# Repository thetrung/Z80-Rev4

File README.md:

# Z80 Homebrew with PIC18/F4520 
Rev4 of Z80 + PIC18/F4520 setup.

### Note
I have never had a real working Z80 before so this board is designed to test that if I can get one.

### 3D Preview 

### Placement (SilkScreen)

### Schematic

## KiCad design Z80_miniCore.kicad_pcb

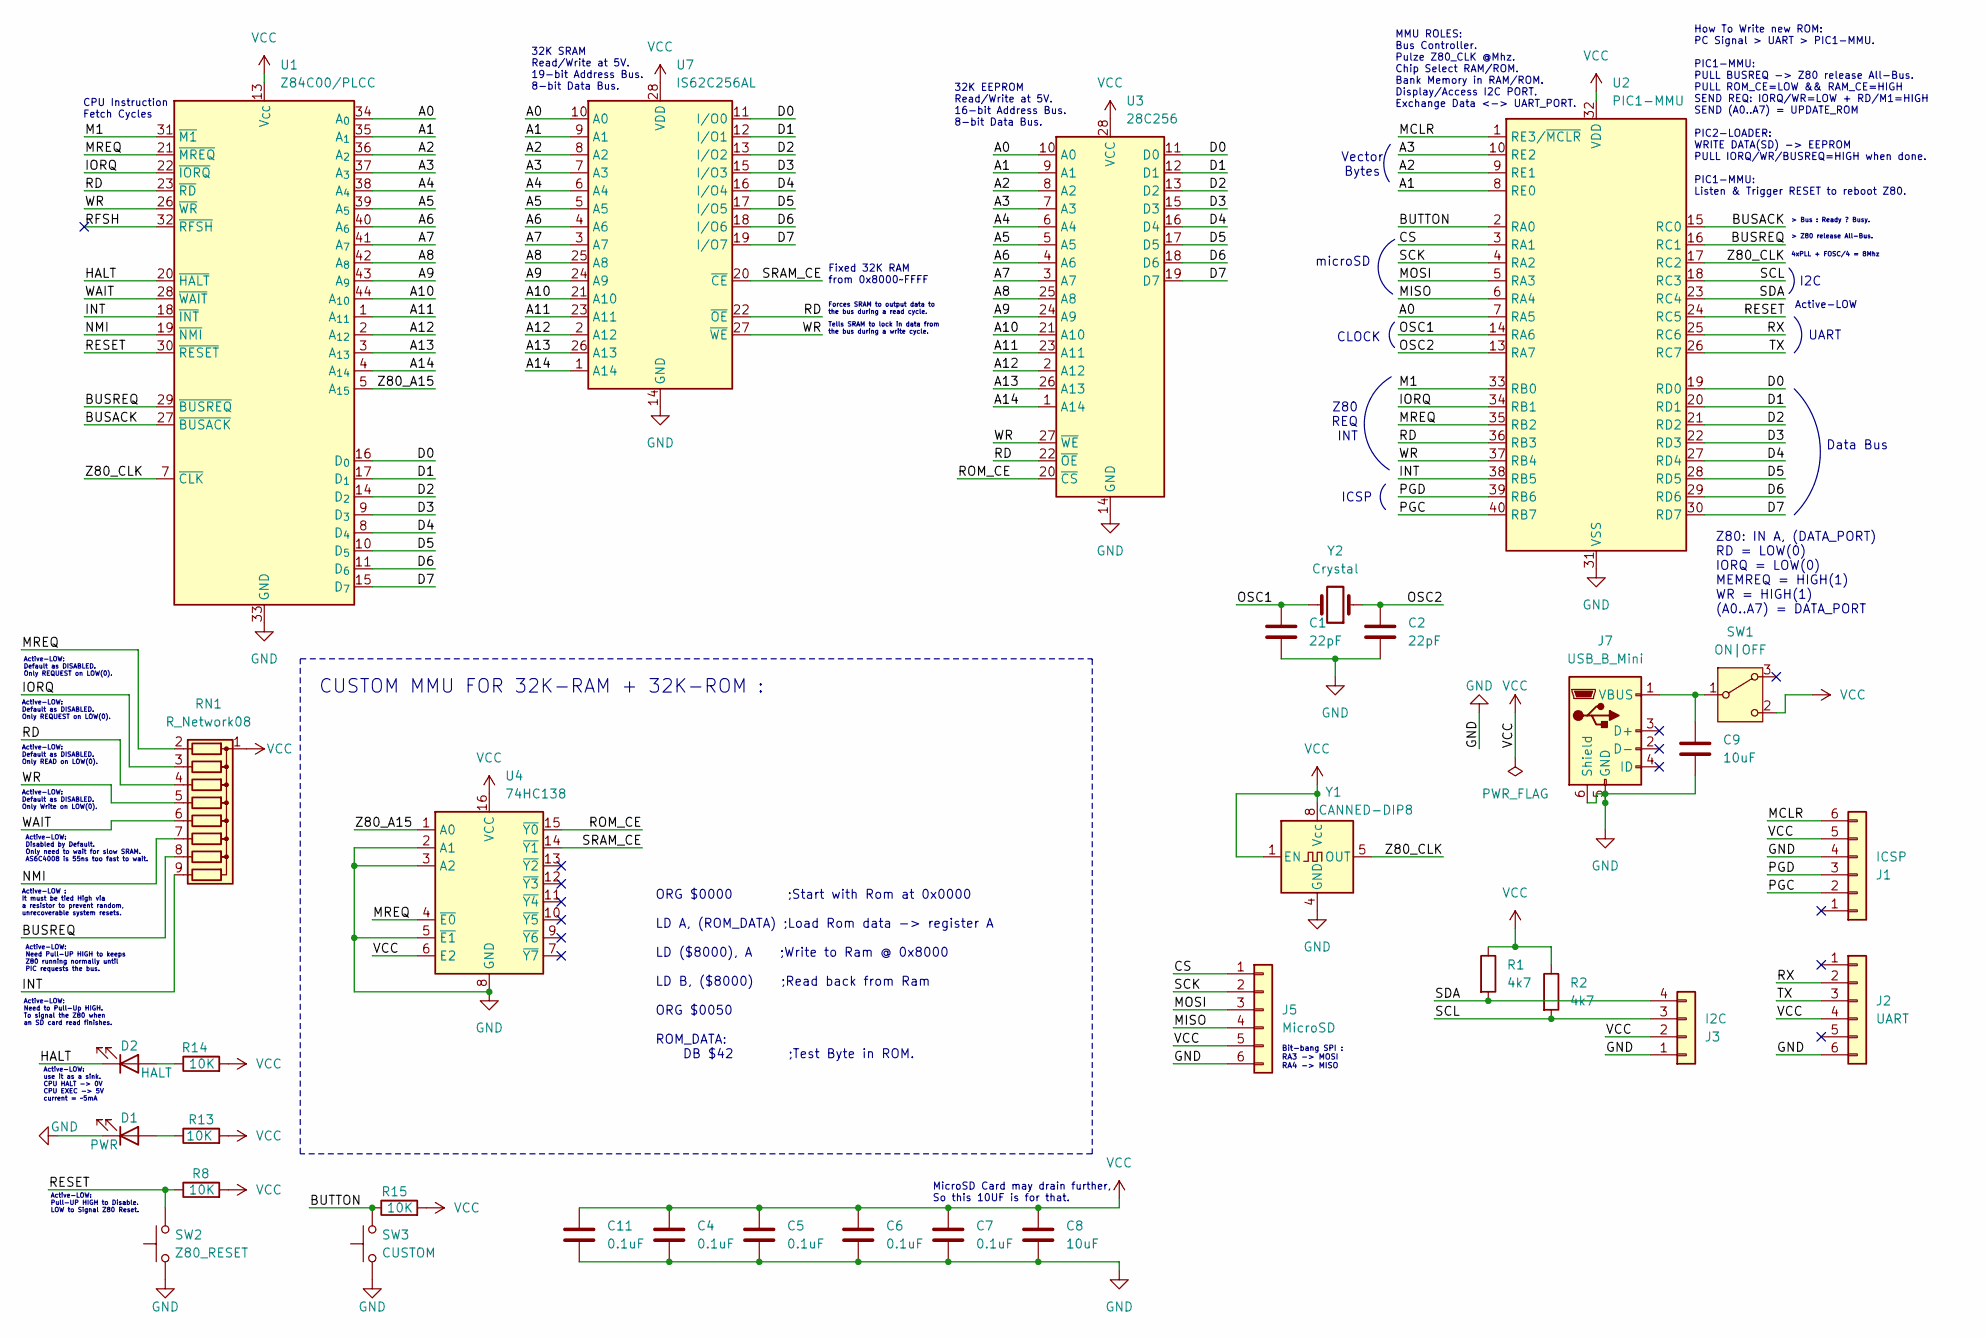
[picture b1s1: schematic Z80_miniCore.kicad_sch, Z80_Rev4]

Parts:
C1, C2: 22pF; C_Disc_D3.4mm_W2.1mm_P2.50mm
C4, C5, C6, C7, C11: 0.1uF; C_Disc_D3.4mm_W2.1mm_P2.50mm
C8, C9: 10uF; C_Radial_D4.0mm_H5.0mm_P1.50mm
D1: PWR; LED_D3.0mm
D2: HALT; LED_D3.0mm
J1: ICSP; PinHeader_1x06_P2.54mm_Horizontal
J2: UART; PinHeader_1x06_P2.54mm_Vertical
J3: I2C; PinHeader_1x04_P2.54mm_Vertical
J5: MicroSD; PinHeader_1x06_P2.54mm_Vertical
J7: USB_B_Mini; USB_MINI_B_90_Angled
R1, R2: 4k7; R_Axial_DIN0207_L6.3mm_D2.5mm_P10.16mm_Horizontal
R8, R13, R14, R15: 10K; R_Axial_DIN0207_L6.3mm_D2.5mm_P10.16mm_Horizontal
RN1: R_Network08; R_Array_SIP9
SW1: ON|OFF; SW_Slide-03_Wuerth-WS-SLTV_10x2.5x6.4_P2.54mm
SW2: Z80_RESET; SW_PUSH_6mm
SW3: CUSTOM; SW_PUSH_6mm
U1: Z84C00/PLCC; PLCC-44_THT-Socket
U2: PIC1-MMU; DIP-40_W15.24mm
U3: 28C256; DIP-28_W15.24mm
U4: 74HC138; DIP-16_W7.62mm
U7: IS62C256AL; DIP-28_W15.24mm
Y1: CANNED-DIP8; Oscillator_DIP-8
Y2: Crystal; Crystal_HC49-4H_Vertical

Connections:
/A0: U1.34 (A_{0}), U2.7 (RA5), U3.10 (A0), U7.10 (A0)
/A1: U1.35 (A_{1}), U2.8 (RE0), U3.9 (A1), U7.9 (A1)
/A2: U1.36 (A_{2}), U2.9 (RE1), U3.8 (A2), U7.8 (A2)
/A3: U1.37 (A_{3}), U2.10 (RE2), U3.7 (A3), U7.7 (A3)
/A4: U1.38 (A_{4}), U3.6 (A4), U7.6 (A4)
/A5: U1.39 (A_{5}), U3.5 (A5), U7.5 (A5)
/A6: U1.40 (A_{6}), U3.4 (A6), U7.4 (A6)
/A7: U1.41 (A_{7}), U3.3 (A7), U7.3 (A7)
/A8: U1.42 (A_{8}), U3.25 (A8), U7.25 (A8)
/A9: U1.43 (A_{9}), U3.24 (A9), U7.24 (A9)
/A10: U1.44 (A_{10}), U3.21 (A10), U7.21 (A10)
/A11: U1.1 (A_{11}), U3.23 (A11), U7.23 (A11)
/A12: U1.2 (A_{12}), U3.2 (A12), U7.2 (A12)
/A13: U1.3 (A_{13}), U3.26 (A13), U7.26 (A13)
/A14: U1.4 (A_{14}), U3.1 (A14), U7.1 (A14)
/BUSACK: U1.27 (~BUSACK), U2.15 (RC0)
/BUSREQ: RN1.8 (R7), U1.29 (~BUSREQ), U2.16 (RC1)
/BUTTON: R15.1, SW3.2, U2.2 (RA0)
/CS: J5.1, U2.3 (RA1)
/D0: U1.16 (D_{0}), U2.19 (RD0), U3.11 (D0), U7.11 (I/O0)
/D1: U1.17 (D_{1}), U2.20 (RD1), U3.12 (D1), U7.12 (I/O1)
/D2: U1.14 (D_{2}), U2.21 (RD2), U3.13 (D2), U7.13 (I/O2)
/D3: U1.9 (D_{3}), U2.22 (RD3), U3.15 (D3), U7.15 (I/O3)
/D4: U1.8 (D_{4}), U2.27 (RD4), U3.16 (D4), U7.16 (I/O4)
/D5: U1.10 (D_{5}), U2.28 (RD5), U3.17 (D5), U7.17 (I/O5)
/D6: U1.11 (D_{6}), U2.29 (RD6), U3.18 (D6), U7.18 (I/O6)
/D7: U1.15 (D_{7}), U2.30 (RD7), U3.19 (D7), U7.19 (I/O7)
/HALT: D2.1 (K), U1.20 (~HALT)
/INT: RN1.9 (R8), U1.18 (~INT), U2.38 (RB5)
/IORQ: RN1.3 (R2), U1.22 (~IORQ), U2.34 (RB1)
/M1: U1.31 (~M1), U2.33 (RB0)
/MCLR: J1.6, U2.1 (RE3/~MCLR)
/MISO: J5.4, U2.6 (RA4)
/MOSI: J5.3, U2.5 (RA3)
/MREQ: RN1.2 (R1), U1.21 (~MREQ), U2.35 (RB2), U4.4 (~E0)
/NMI: RN1.7 (R6), U1.19 (~NMI)
/OSC1: C1.1, U2.14 (RA6), Y2.2
/OSC2: C2.1, U2.13 (RA7), Y2.1
/PGC: J1.2, U2.40 (RB7)
/PGD: J1.3, U2.39 (RB6)
/RD: RN1.4 (R3), U1.23 (~RD), U2.36 (RB3), U3.22 (~OE), U7.22 (~OE)
/RESET: R8.1, SW2.2, U1.30 (~RESET), U2.24 (RC5)
/RFSH: U1.32 (~RFSH)
/ROM_CE: U3.20 (~CS), U4.15 (~Y0)
/RX: J2.2, U2.25 (RC6)
/SCK: J5.2, U2.4 (RA2)
/SCL: J3.3, R2.2, U2.18 (RC3)
/SDA: J3.4, R1.2, U2.23 (RC4)
/SRAM_CE: U4.14 (~Y1), U7.20 (~CE)
/TX: J2.3, U2.26 (RC7)
/WAIT: RN1.6 (R5), U1.28 (~WAIT)
/WR: RN1.5 (R4), U1.26 (~WR), U2.37 (RB4), U3.27 (~WE), U7.27 (~WE)
/Z80_A15: U1.5 (A_{15}), U4.1 (A0)
/Z80_CLK: U1.7 (~CLK), U2.17 (RC2), Y1.5 (OUT)
GND: C1.2, C2.2, C4.1, C5.1, C6.1, C7.1, C8.1, C9.1, C11.1, D1.1 (K), J1.4, J2.6, J3.1, J5.6, J7.5 (GND), J7.6 (Shield), SW2.1, SW3.1, U1.33 (GND), U2.12 (VSS), U2.31 (VSS), U3.14 (GND), U4.2 (A1), U4.3 (A2), U4.5 (~E1), U4.8 (GND), U7.14 (GND), Y1.4 (GND)
unnamed: D1.2 (A), R13.1
unnamed: D2.2 (A), R14.1
unnamed: C9.2, J7.1 (VBUS), SW1.1 (B)
VCC: C4.2, C5.2, C6.2, C7.2, C8.2, C11.2, J1.5, J2.4, J3.2, J5.5, R1.1, R2.1, R8.2, R13.2, R14.2, R15.2, RN1.1 (common), SW1.2 (C), U1.13 (V_{CC}), U2.11 (VDD), U2.32 (VDD), U3.28 (VCC), U4.6 (E2), U4.16 (VCC), U7.28 (VDD), Y1.1 (EN), Y1.8 (Vcc)

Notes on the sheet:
microSD
Active-LOW: Default as DISABLED. Only REQUEST on LOW(0).
Active-LOW: Need to Pull-Up HIGH. To signal the Z80 when an SD card read finishes.
Tells SRAM to lock in data from the bus during a write cycle.
32K SRAM Read/Write at 5V. 19-bit Address Bus. 8-bit Data Bus.
Active-LOW: use it as a sink. CPU HALT -> 0V CPU EXEC -> 5V current = ~5mA
Active-LOW: Default as DISABLED. Only READ on LOW(0).
ICSP
CLOCK
> Bus : Ready ? Busy.
ORG $0000 ;Start with Rom at 0x0000 LD A, (ROM_DATA) ;Load Rom data -> register A LD ($8000), A ;Write to Ram @ 0x8000 LD B, ($8000) ;Read back from Ram ORG $0050 ROM_DATA: DB $42 ;Test Byte in ROM.
Data Bus
Z80 REQ INT
Forces SRAM to output data to the bus during a read cycle.
MMU ROLES: Bus Controller. Pulze Z80_CLK @Mhz. Chip Select RAM/ROM. Bank Memory in RAM/ROM. Display/Access I2C PORT. Exchange Data <-> UART_PORT.
32K EEPROM Read/Write at 5V. 16-bit Address Bus. 8-bit Data Bus.
Active-LOW: Disabled by Default. Only need to wait for slow SRAM. AS6C4008 is 55ns too fast to wait.
Active-LOW: Need Pull-UP HIGH to keeps Z80 running normally until PIC requests the bus.
I2C
MicroSD Card may drain further, So this 10UF is for that.
Active-LOW : It must be tied High via a resistor to prevent random, unrecoverable system resets.
Active-LOW: Pull-UP HIGH to Disable. LOW to Signal Z80 Reset.
4xPLL + FOSC/4 = 8Mhz
Active-LOW: Default as DISABLED. Only Write on LOW(0).
Fixed 32K RAM from 0x8000~FFFF
CUSTOM MMU FOR 32K-RAM + 32K-ROM :
Bit-bang SPI : RA3 -> MOSI RA4 -> MISO
Active-LOW
CPU Instruction Fetch Cycles
How To Write new ROM: PC Signal > UART > PIC1-MMU. PIC1-MMU: PULL BUSREQ -> Z80 release All-Bus. PULL ROM_CE=LOW && RAM_CE=HIGH SEND REQ: IORQ/WR=LOW + RD/M1=HIGH SEND (A0..A7) = UPDATE_ROM PIC2-LOADER: WRITE DATA(SD) -> EEPROM PULL IORQ/WR/BUSREQ=HIGH when done. PIC1-MMU: Listen & Trigger RESET to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
> Z80 release All-Bus.
UART
Z80: IN A, (DATA_PORT) RD = LOW(0) IORQ = LOW(0) MEMREQ = HIGH(1) WR = HIGH(1) (A0..A7) = DATA_PORT
Vector Bytes

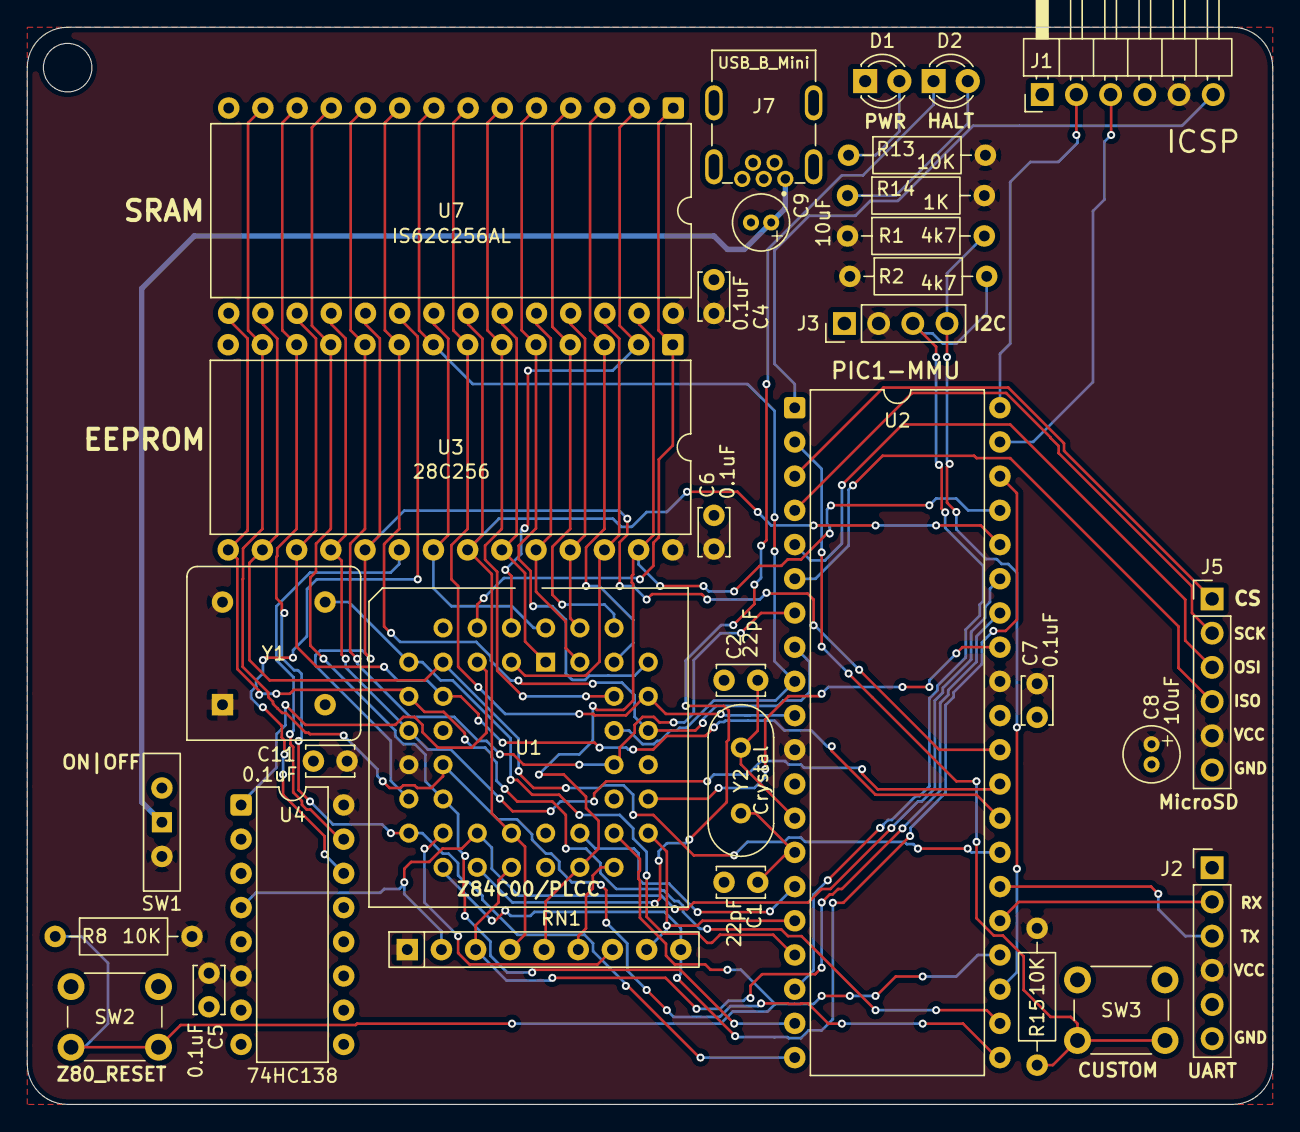
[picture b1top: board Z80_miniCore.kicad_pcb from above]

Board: 2 copper layers, 92.5 x 80.0 mm, 33 parts (0 on the bottom side), 58 nets.
